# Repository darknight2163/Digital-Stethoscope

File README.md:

# Digital-Stethoscope
Implementation of the digital stethoscope with PCB components

# Abstract
In most of the countries throughout the world, heart disease is the leading cause of mortality. Cardiovascular illnesses caused 17.5 million deaths in 2012, or three out of every ten fatalities. The noises that the heart makes are connected to and constitute the majority of heart diseases. Heart auscultation, often known as hearing the heartbeat, has been a crucial technique for the early detection of cardiac malfunction. Traditional auscultation calls for a strong clinical background and empathetic listening abilities. A new branch of computer-aided auscultation has emerged due to to the development of the electronic stethoscope.
# Problem Statement
Implementation of the digital stethoscope with  components.
# Objective 
A circuit picks up the sound vibrations from the diaphragm of the stethoscope (microphone) and convert it to electronic signals that are then amplified and can be heard through a speaker loud enough that connecting to ears is not required and no sound is missed (even by less experienced practitioners). 
Using the Bluetooth module and arduino, we will then transfer this data to a Bluetooth terminal window. We will build an app which can correctly receive and show audio data from the digital stethoscope.
# Schematic Diagram of Circuit 

# Work Plan
|Sl. No.|Task|Task Description|Duration|
|---|---|---|---|
|1|Problem statement analysis| 1. Research different microphone and amplifier designs 2. Research Bluetooth module specifications 3. Identify the components needed|1week|
|2|Microphone and amplifier circuit|1. Create a schematic of the stethoscope's circuit using a computer-aided design (CAD) program 2. Assemble the circuit on breadboard and test it|1week|
|3|Filter and driver circuit|1. Prepare BOM and purchase the necessary components for the circuit 2. Assemble the circuit on breadboard and test it|1week|
|4|PCB Soldering|1. Assemble the PCB board, placing all the components and soldering them in place|2week|
|5|Adding LED to the PCB board circuit|1. Adding LED to the PCB board which will glow in sync with the heartbeat signal|1week|
|6|Final inspection of PCB board|1. Perform a final inspection and test to ensure that the board is functioning properly|1week|
|7|Implementing the wireless (Bluetooth) module to the stethoscope's circuit|1. Connect the Bluetooth module to the stethoscope's circuit 2. Test the stethoscope's Bluetooth functionality|1week|
|8|Develop the mobile app to interface the stethoscope|1. Identify the necessary features of the app 2. Choose a development platform and programming language 3. Design and code the app 4. Testing the app|3week|
|9|Integrate the hardware and software|1. Connect the Bluetooth module to the stethoscope's circuit 2. Test the stethoscope's Bluetooth functionality 3. Ensure that the app can properly receive and display audio data from the stethoscope|1week|
|10|Final testing and quality control|1. Test the stethoscope under various conditions 2. Make any necessary adjustments or repairs|1week|
|11|Final project documentation|1. Prepare final report|1week|

# PCB designed using KiCAD

# PCB routing

# References
Electronic Stethoscope (Circuit Diagram): [circuit](http://www.diy-electronic-projects.com/p236-Electronic-Stethoscope) 
Electronic Stethoscope Article: [diy](https://people.ece.cornell.edu/land/courses/ece4760/FinalProjects/s2012/myw9_gdd9/myw9_gdd9/)

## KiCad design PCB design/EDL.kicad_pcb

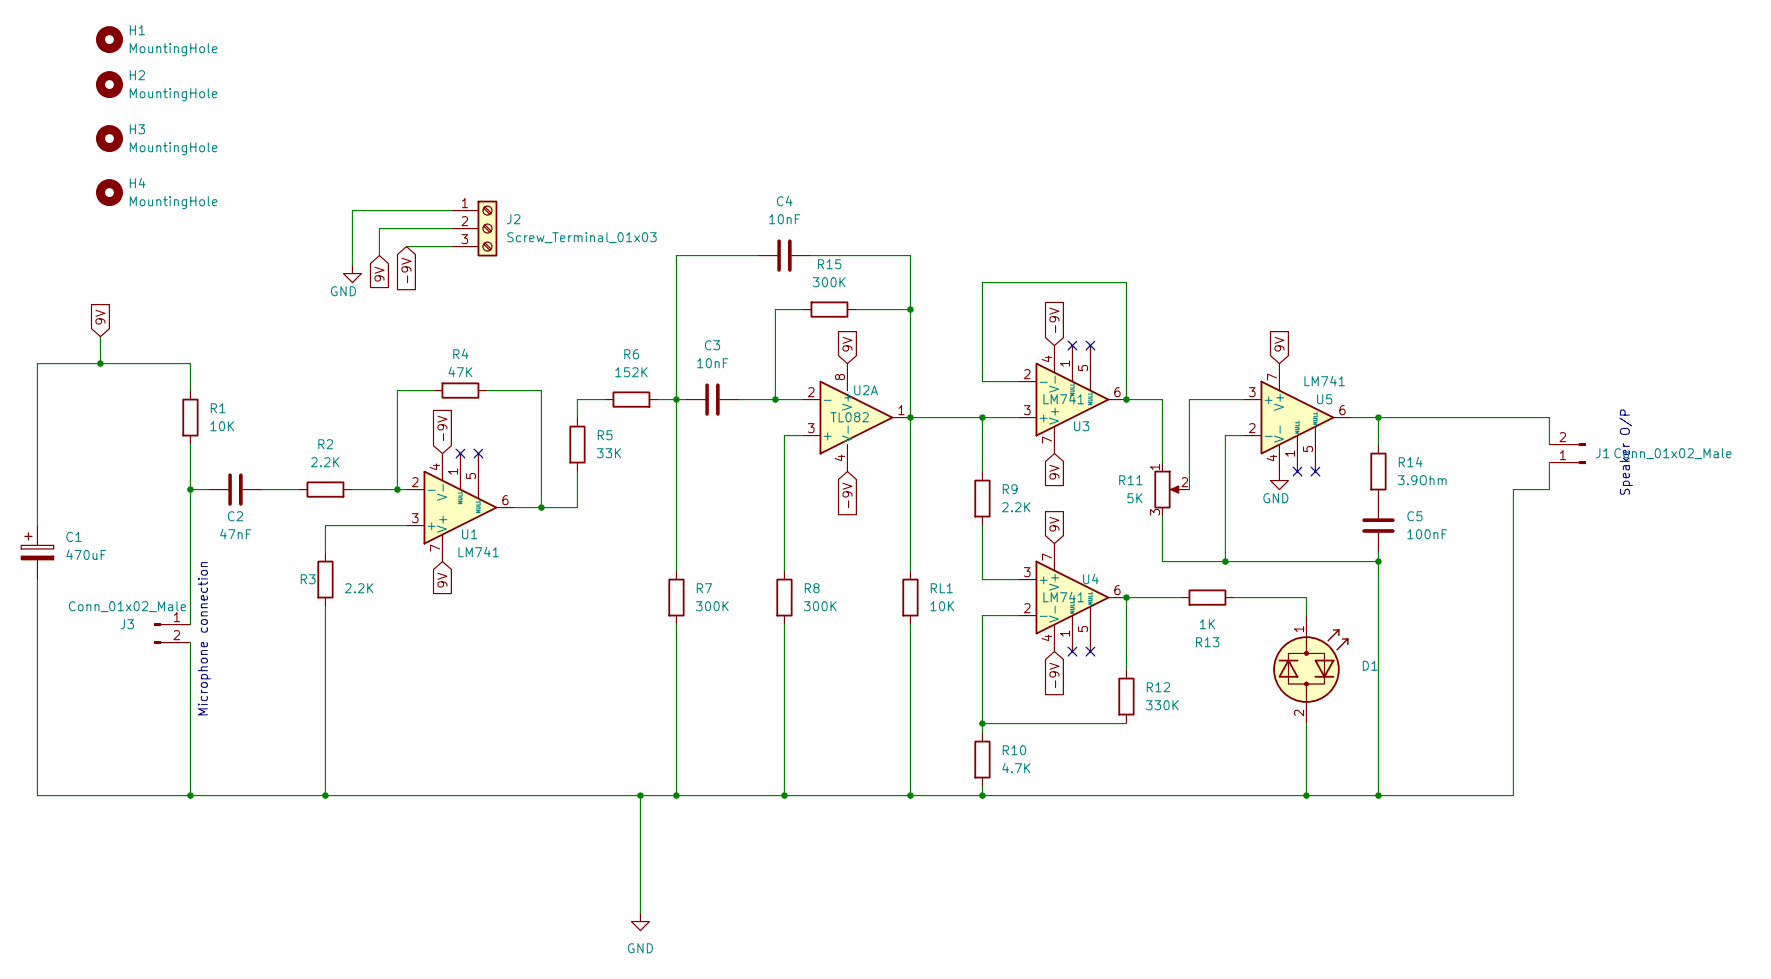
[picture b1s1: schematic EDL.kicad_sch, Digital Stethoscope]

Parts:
C1: 470uF; CP_Elec_8x11.9
C2: 47nF; C_0805_2012Metric_Pad1.18x1.45mm_HandSolder
C3, C4: 10nF; C_0805_2012Metric_Pad1.18x1.45mm_HandSolder
C5: 100nF; C_0805_2012Metric_Pad1.18x1.45mm_HandSolder
D1: LED_Dual_Bidirectional; LED_0805_2012Metric_Pad1.15x1.40mm_HandSolder
H1, H2, H3, H4: MountingHole; MountingHole_2.5mm_Pad_TopOnly
J1, J3: Conn_01x02_Male; PinHeader_1x02_P2.54mm_Vertical
J2: Screw_Terminal_01x03; TerminalBlock_Phoenix_MKDS-1,5-3_1x03_P5.00mm_Horizontal
R1: 10K; R_0805_2012Metric_Pad1.20x1.40mm_HandSolder
R2, R3, R9: 2.2K; R_0805_2012Metric_Pad1.20x1.40mm_HandSolder
R4: 47K; R_0805_2012Metric_Pad1.20x1.40mm_HandSolder
R5: 33K; R_0805_2012Metric_Pad1.20x1.40mm_HandSolder
R6: 152K; R_0805_2012Metric_Pad1.20x1.40mm_HandSolder
R7, R8, R15: 300K; R_0805_2012Metric_Pad1.20x1.40mm_HandSolder
R10: 4.7K; R_0805_2012Metric_Pad1.20x1.40mm_HandSolder
R11: 5K; Potentiometer_Bourns_3386P_Vertical
R12: 330K; R_0805_2012Metric_Pad1.20x1.40mm_HandSolder
R13: 1K; R_0805_2012Metric_Pad1.20x1.40mm_HandSolder
R14: 3.9Ohm; R_0805_2012Metric_Pad1.20x1.40mm_HandSolder
RL1: 10K; R_0805_2012Metric_Pad1.20x1.40mm_HandSolder
U1, U3, U4, U5: LM741; DIP-8_W10.16mm
U2: TL082; DIP-8_W10.16mm

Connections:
9V: C1.1, J2.2, R1.1, U1.7 (V+), U2.8 (V+), U3.7 (V+), U4.7 (V+), U5.7 (V+)
-9V: J2.3, U1.4 (V-), U2.4 (V-), U3.4 (V-), U4.4 (V-)
GND: C1.2, C5.2, D1.2 (AK), J1.1, J2.1, J3.2, R3.2, R7.2, R8.2, R10.2, R11.3, RL1.2, U5.2 (-), U5.4 (V-)
unnamed: C2.1, J3.1, R1.2
unnamed: C2.2, R2.1
unnamed: C3.1, R15.2, U2.2 (-)
unnamed: C3.2, C4.2, R6.2, R7.1
unnamed: C4.1, R9.1, R15.1, RL1.1, U2.1, U3.3 (+)
unnamed: C5.1, R14.2
unnamed: D1.1 (KA), R13.1
unnamed: J1.2, R14.1, U5.6
unnamed: R2.2, R4.2, U1.2 (-)
unnamed: R3.1, U1.3 (+)
unnamed: R4.1, R5.2, U1.6
unnamed: R5.1, R6.1
unnamed: R8.1, U2.3 (+)
unnamed: R9.2, U4.3 (+)
unnamed: R10.1, R12.2, U4.2 (-)
unnamed: R11.1, U3.2 (-), U3.6
unnamed: R11.2, U5.3 (+)
unnamed: R12.1, R13.2, U4.6

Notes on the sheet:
Microphone connection
Speaker O/P

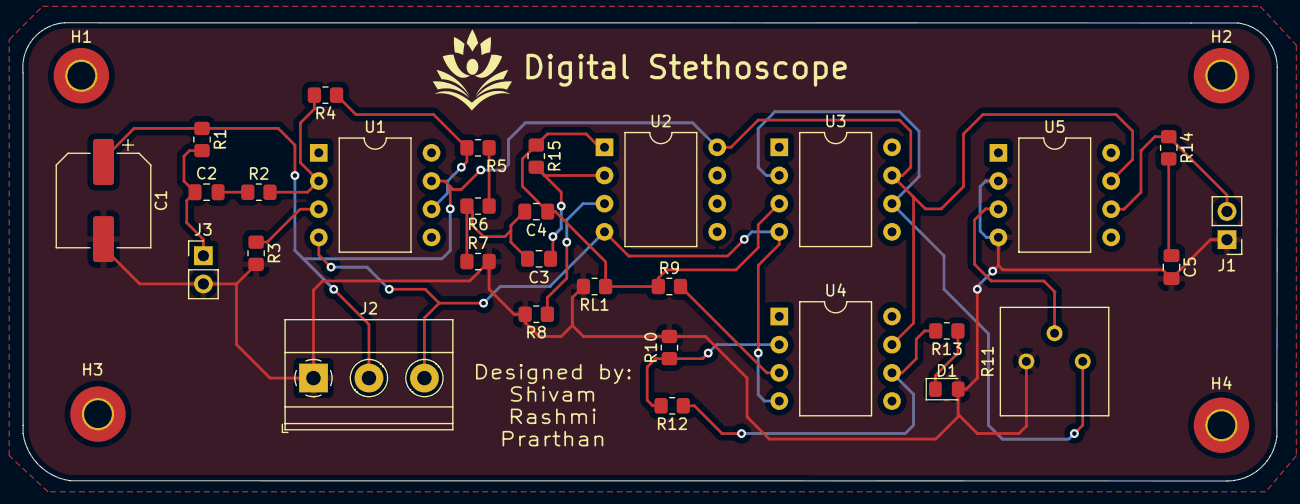
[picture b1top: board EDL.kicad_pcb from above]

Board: 2 copper layers, 113.1 x 41.3 mm, 34 parts (0 on the bottom side), 21 nets.

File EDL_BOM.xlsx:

Id | Designator | Package | Quantity | Designation | Supplier and ref |  | issuing needed
1 | R8,R7,R15 | R_0805_2012Metric_Pad1.20x1.40mm_HandSolder | 3 | 300K |  | Y | yyy
2 | R2,R3,R9 | R_0805_2012Metric_Pad1.20x1.40mm_HandSolder | 3 | 2.2K |  | Y | y,y,y
3 | R5 | R_0805_2012Metric_Pad1.20x1.40mm_HandSolder | 1 | 33K/22k |  | N | y
4 | R4 | R_0805_2012Metric_Pad1.20x1.40mm_HandSolder | 1 | 47K |  | N | y
5 | R13 | R_0805_2012Metric_Pad1.20x1.40mm_HandSolder | 1 | 1K |  | Y | y | n
6 | J1,J3 | PinHeader_1x02_P2.54mm_Vertical | 2 | Conn_01x02_Male |  | Y | nn
7 | R10 | R_0805_2012Metric_Pad1.20x1.40mm_HandSolder | 1 | 4.7K |  | Y | y
8 | R11 | Potentiometer_Bourns_3386P_Vertical | 1 | 5K |  |  | y
9 | C5 | C_0805_2012Metric_Pad1.18x1.45mm_HandSolder | 1 | 100nF |  | Y | y
10 | U4,U5,U3,U1 | DIP-8_W10.16mm | 4 | LM741 |  |  | yyyy
11 | C1 | CP_Elec_8x11.9 | 1 | 470uF |  | Y | y | electrolytic
12 | U2 | DIP-8_W10.16mm | 1 | TL082 |  | Y | y
13 | R14 | R_0805_2012Metric_Pad1.20x1.40mm_HandSolder | 1 | 3.9Ohm |  | Y | y
14 | D1 | LED_0805_2012Metric_Pad1.15x1.40mm_HandSolder | 1 | LED_Dual_Bidirectional |  | N | y
15 | R6 | R_0805_2012Metric_Pad1.20x1.40mm_HandSolder | 1 | 152K |  | Y | y
16 | H3,H1,H2,H4 | MountingHole_2.5mm_Pad_TopOnly | 4 | MountingHole |  | Y | n
17 | C4,C3 | C_0805_2012Metric_Pad1.18x1.45mm_HandSolder | 2 | 10nF |  | Y | yy
18 | J2 | TerminalBlock_Phoenix_MKDS-1,5-3_1x03_P5.00mm_Horizontal | 1 | Screw_Terminal_01x03 |  | Y | y
19 | R12 | R_0805_2012Metric_Pad1.20x1.40mm_HandSolder | 1 | 330K |  | N | y
20 | R1,RL1 | R_0805_2012Metric_Pad1.20x1.40mm_HandSolder | 2 | 10K |  | Y | yy
21 | C2 | C_0805_2012Metric_Pad1.18x1.45mm_HandSolder | 1 | 47nF |  | Y | y
